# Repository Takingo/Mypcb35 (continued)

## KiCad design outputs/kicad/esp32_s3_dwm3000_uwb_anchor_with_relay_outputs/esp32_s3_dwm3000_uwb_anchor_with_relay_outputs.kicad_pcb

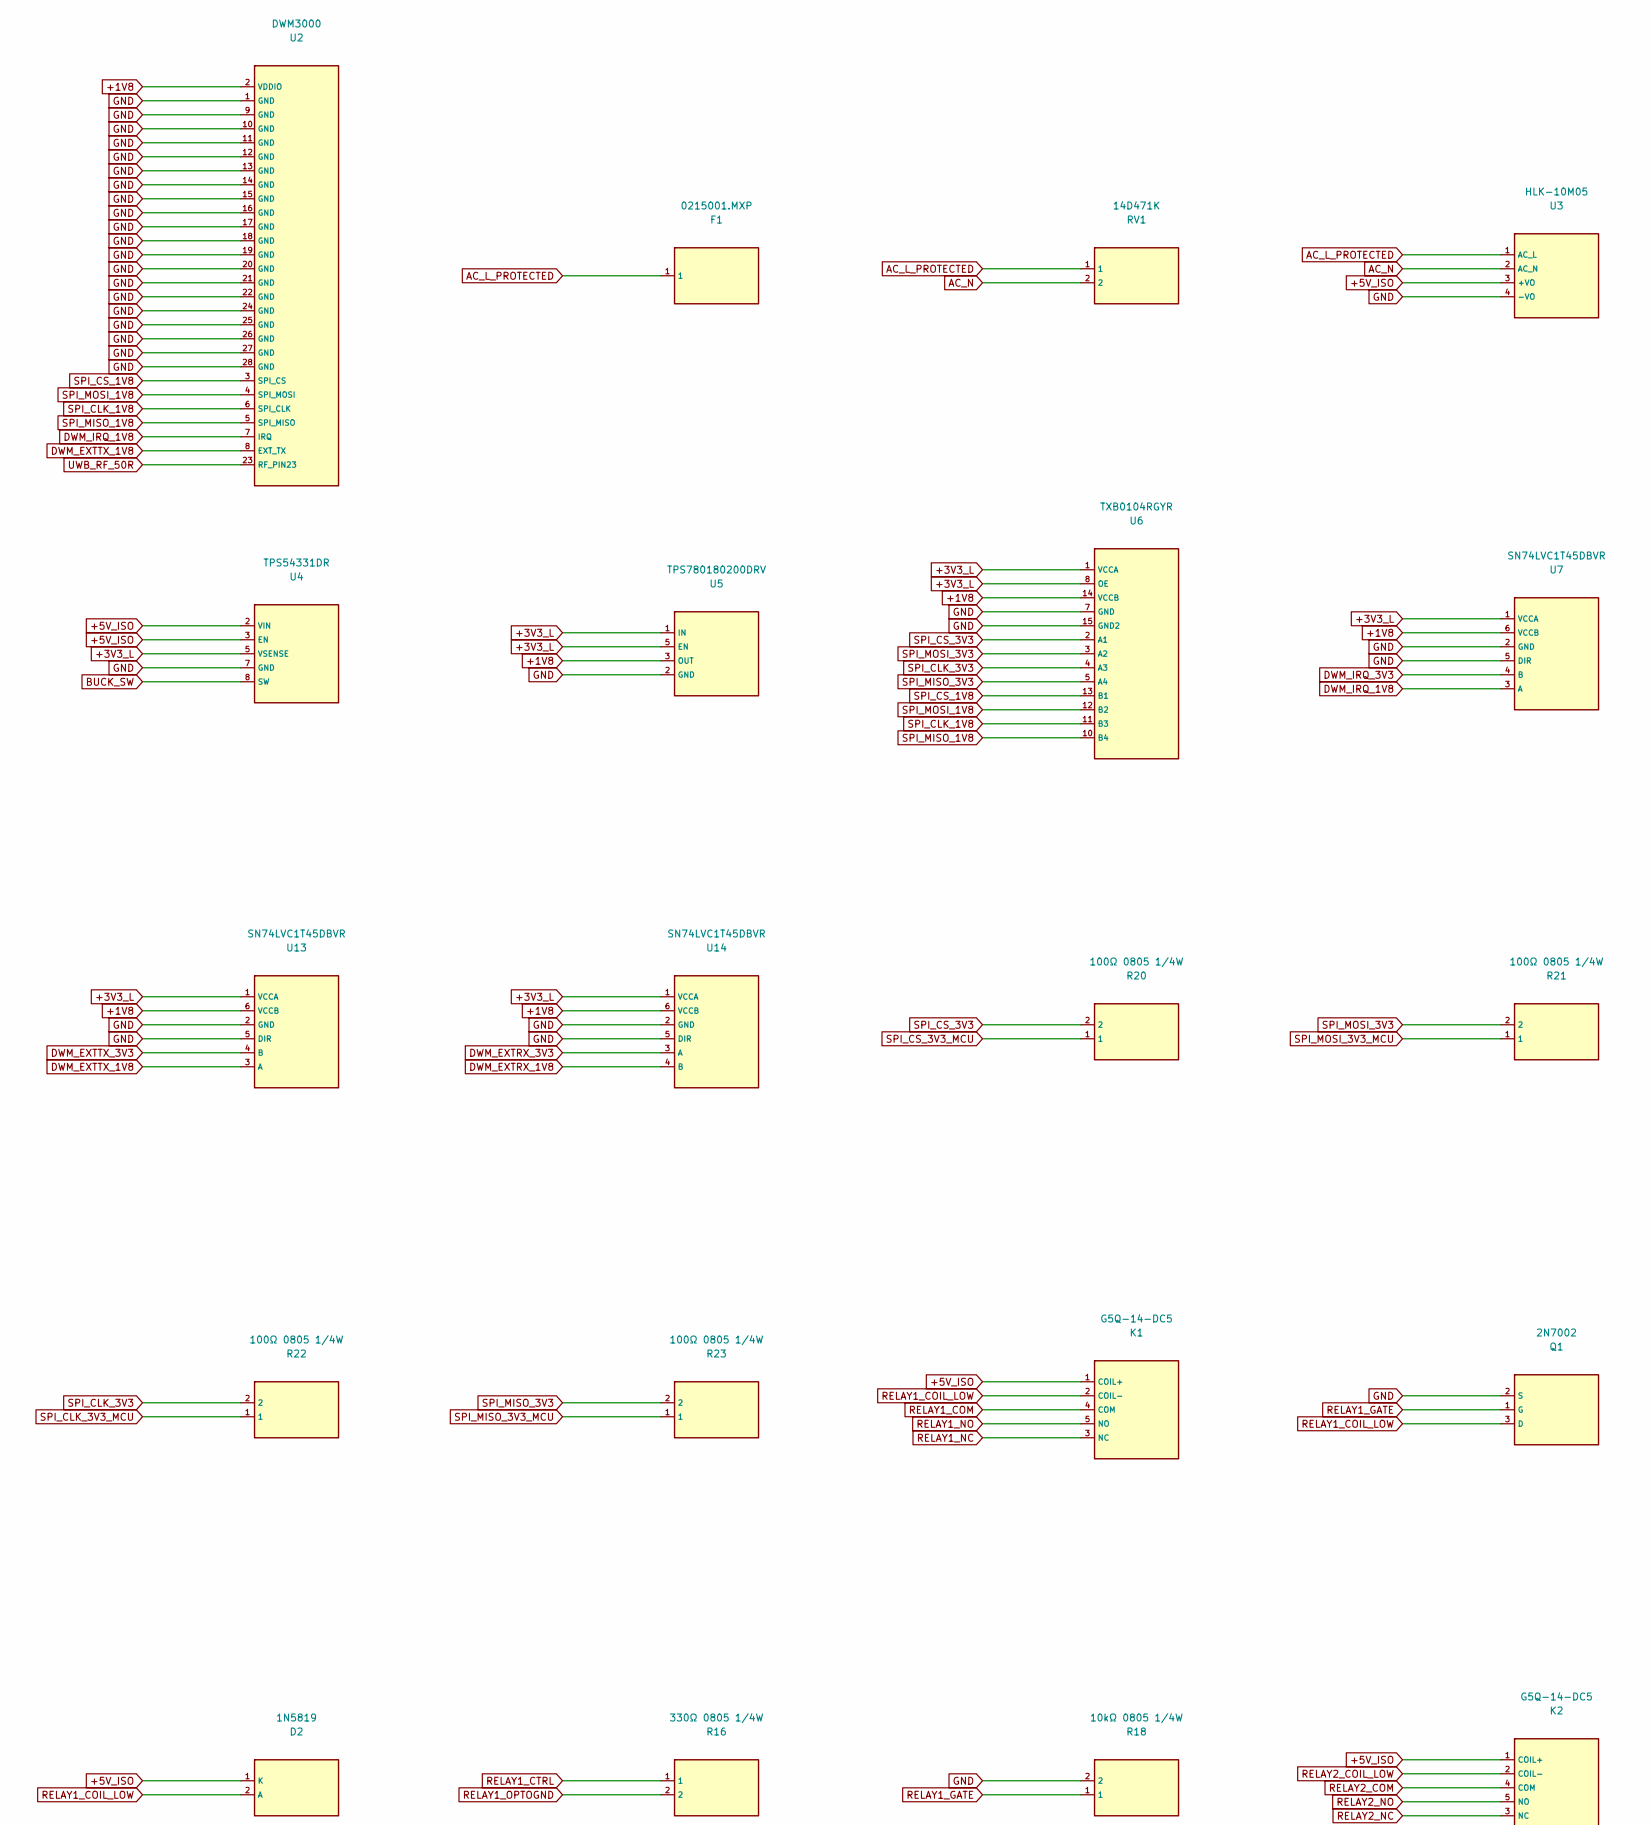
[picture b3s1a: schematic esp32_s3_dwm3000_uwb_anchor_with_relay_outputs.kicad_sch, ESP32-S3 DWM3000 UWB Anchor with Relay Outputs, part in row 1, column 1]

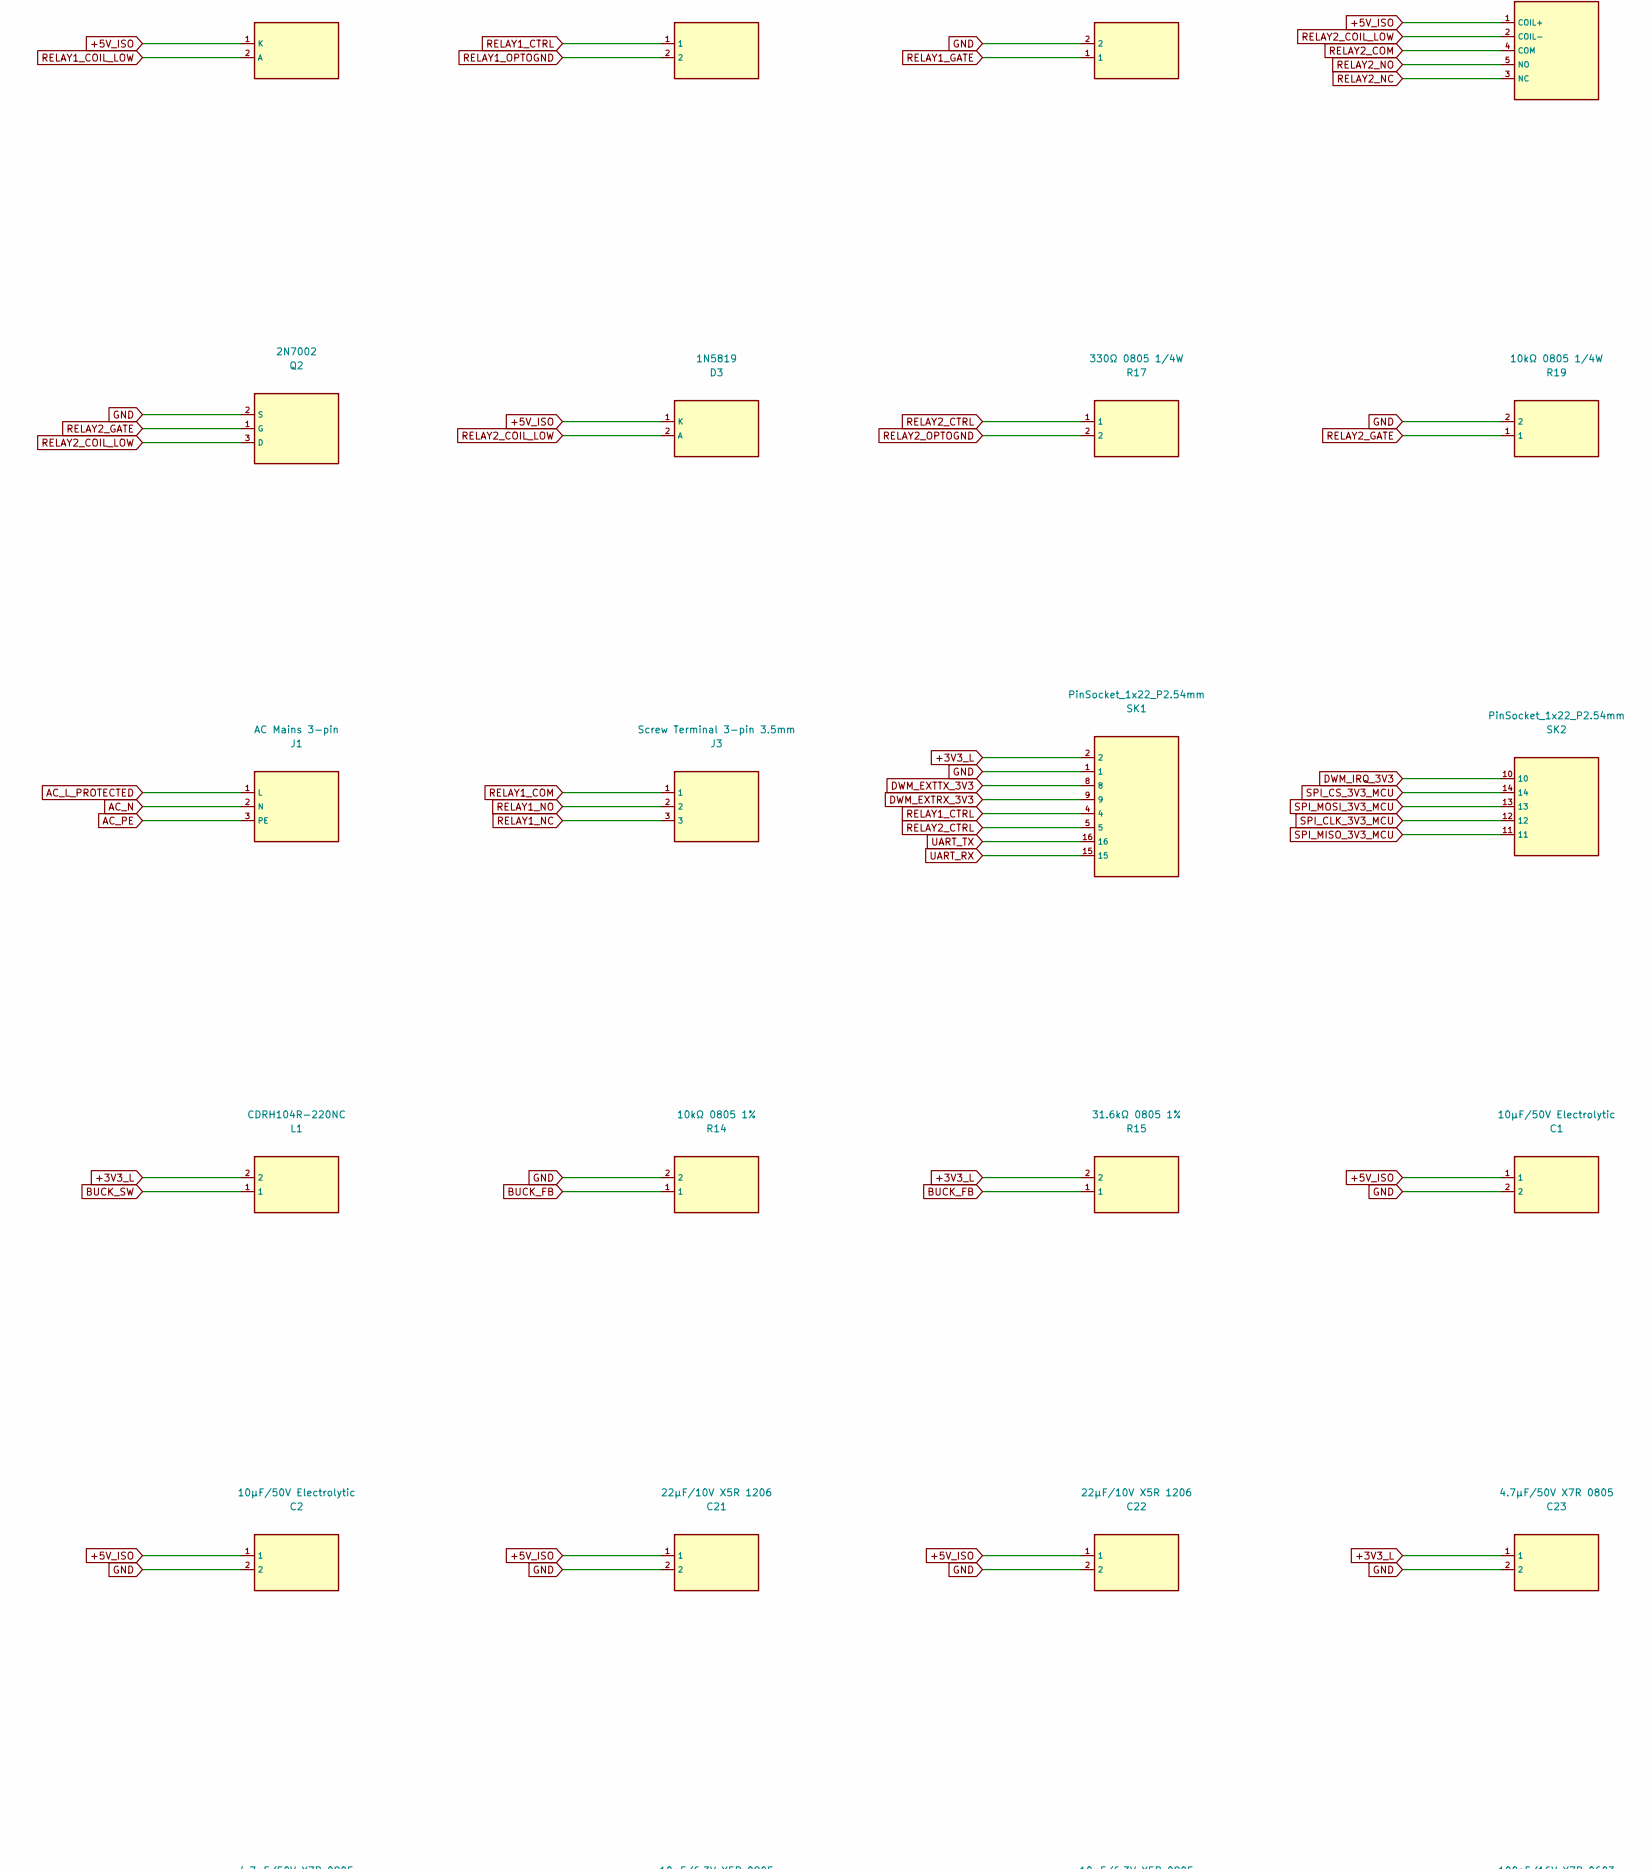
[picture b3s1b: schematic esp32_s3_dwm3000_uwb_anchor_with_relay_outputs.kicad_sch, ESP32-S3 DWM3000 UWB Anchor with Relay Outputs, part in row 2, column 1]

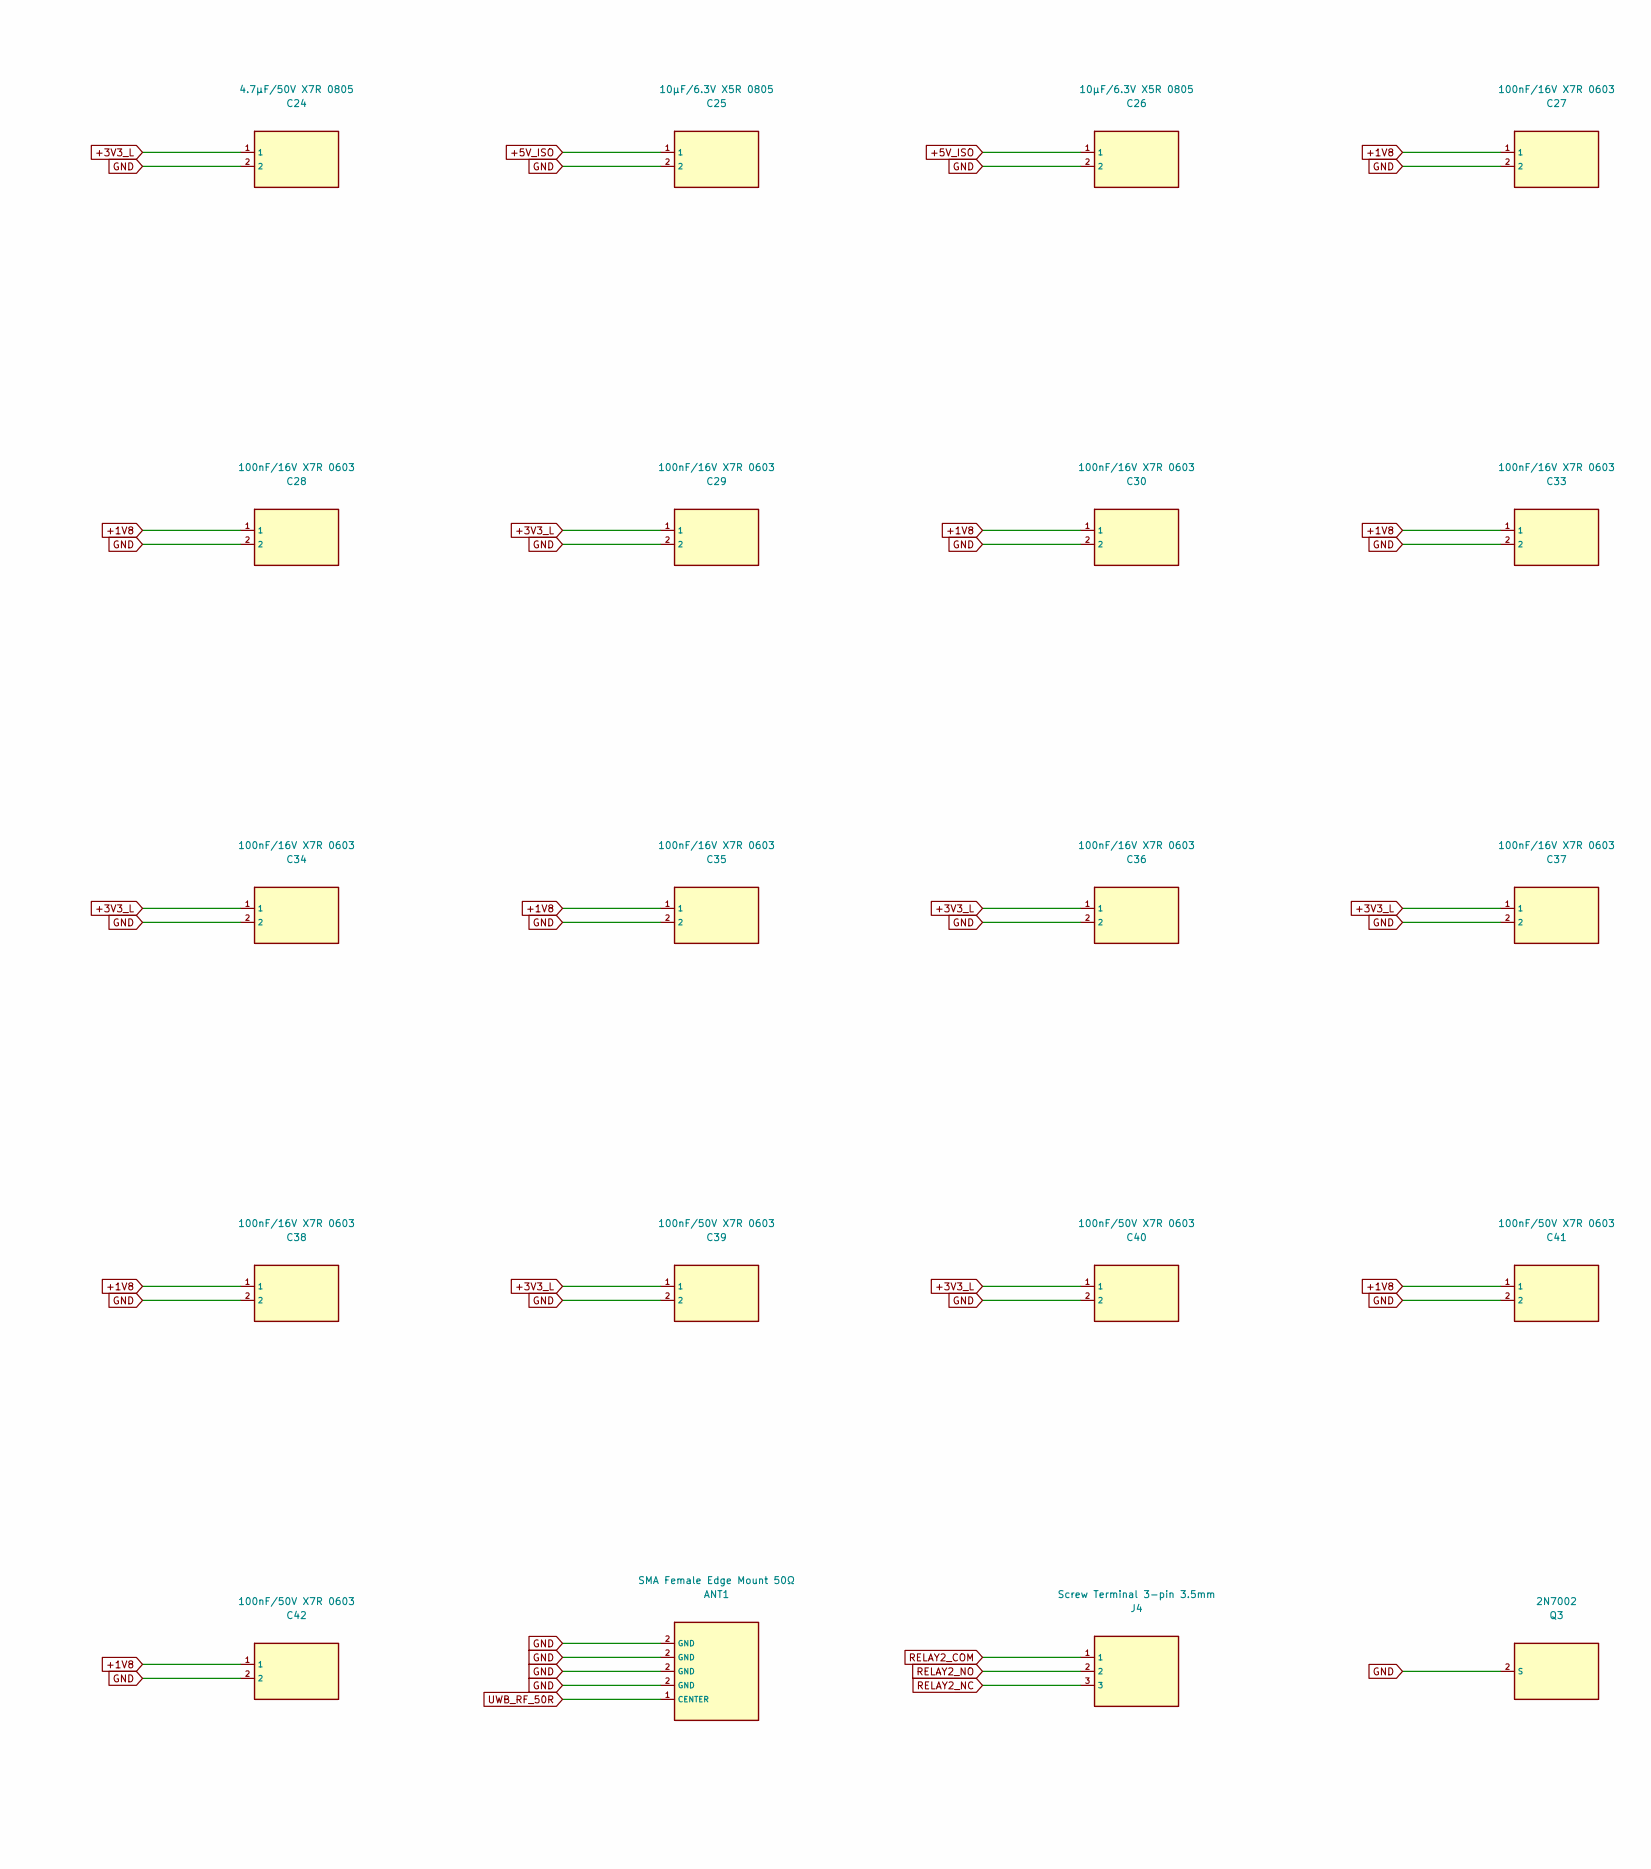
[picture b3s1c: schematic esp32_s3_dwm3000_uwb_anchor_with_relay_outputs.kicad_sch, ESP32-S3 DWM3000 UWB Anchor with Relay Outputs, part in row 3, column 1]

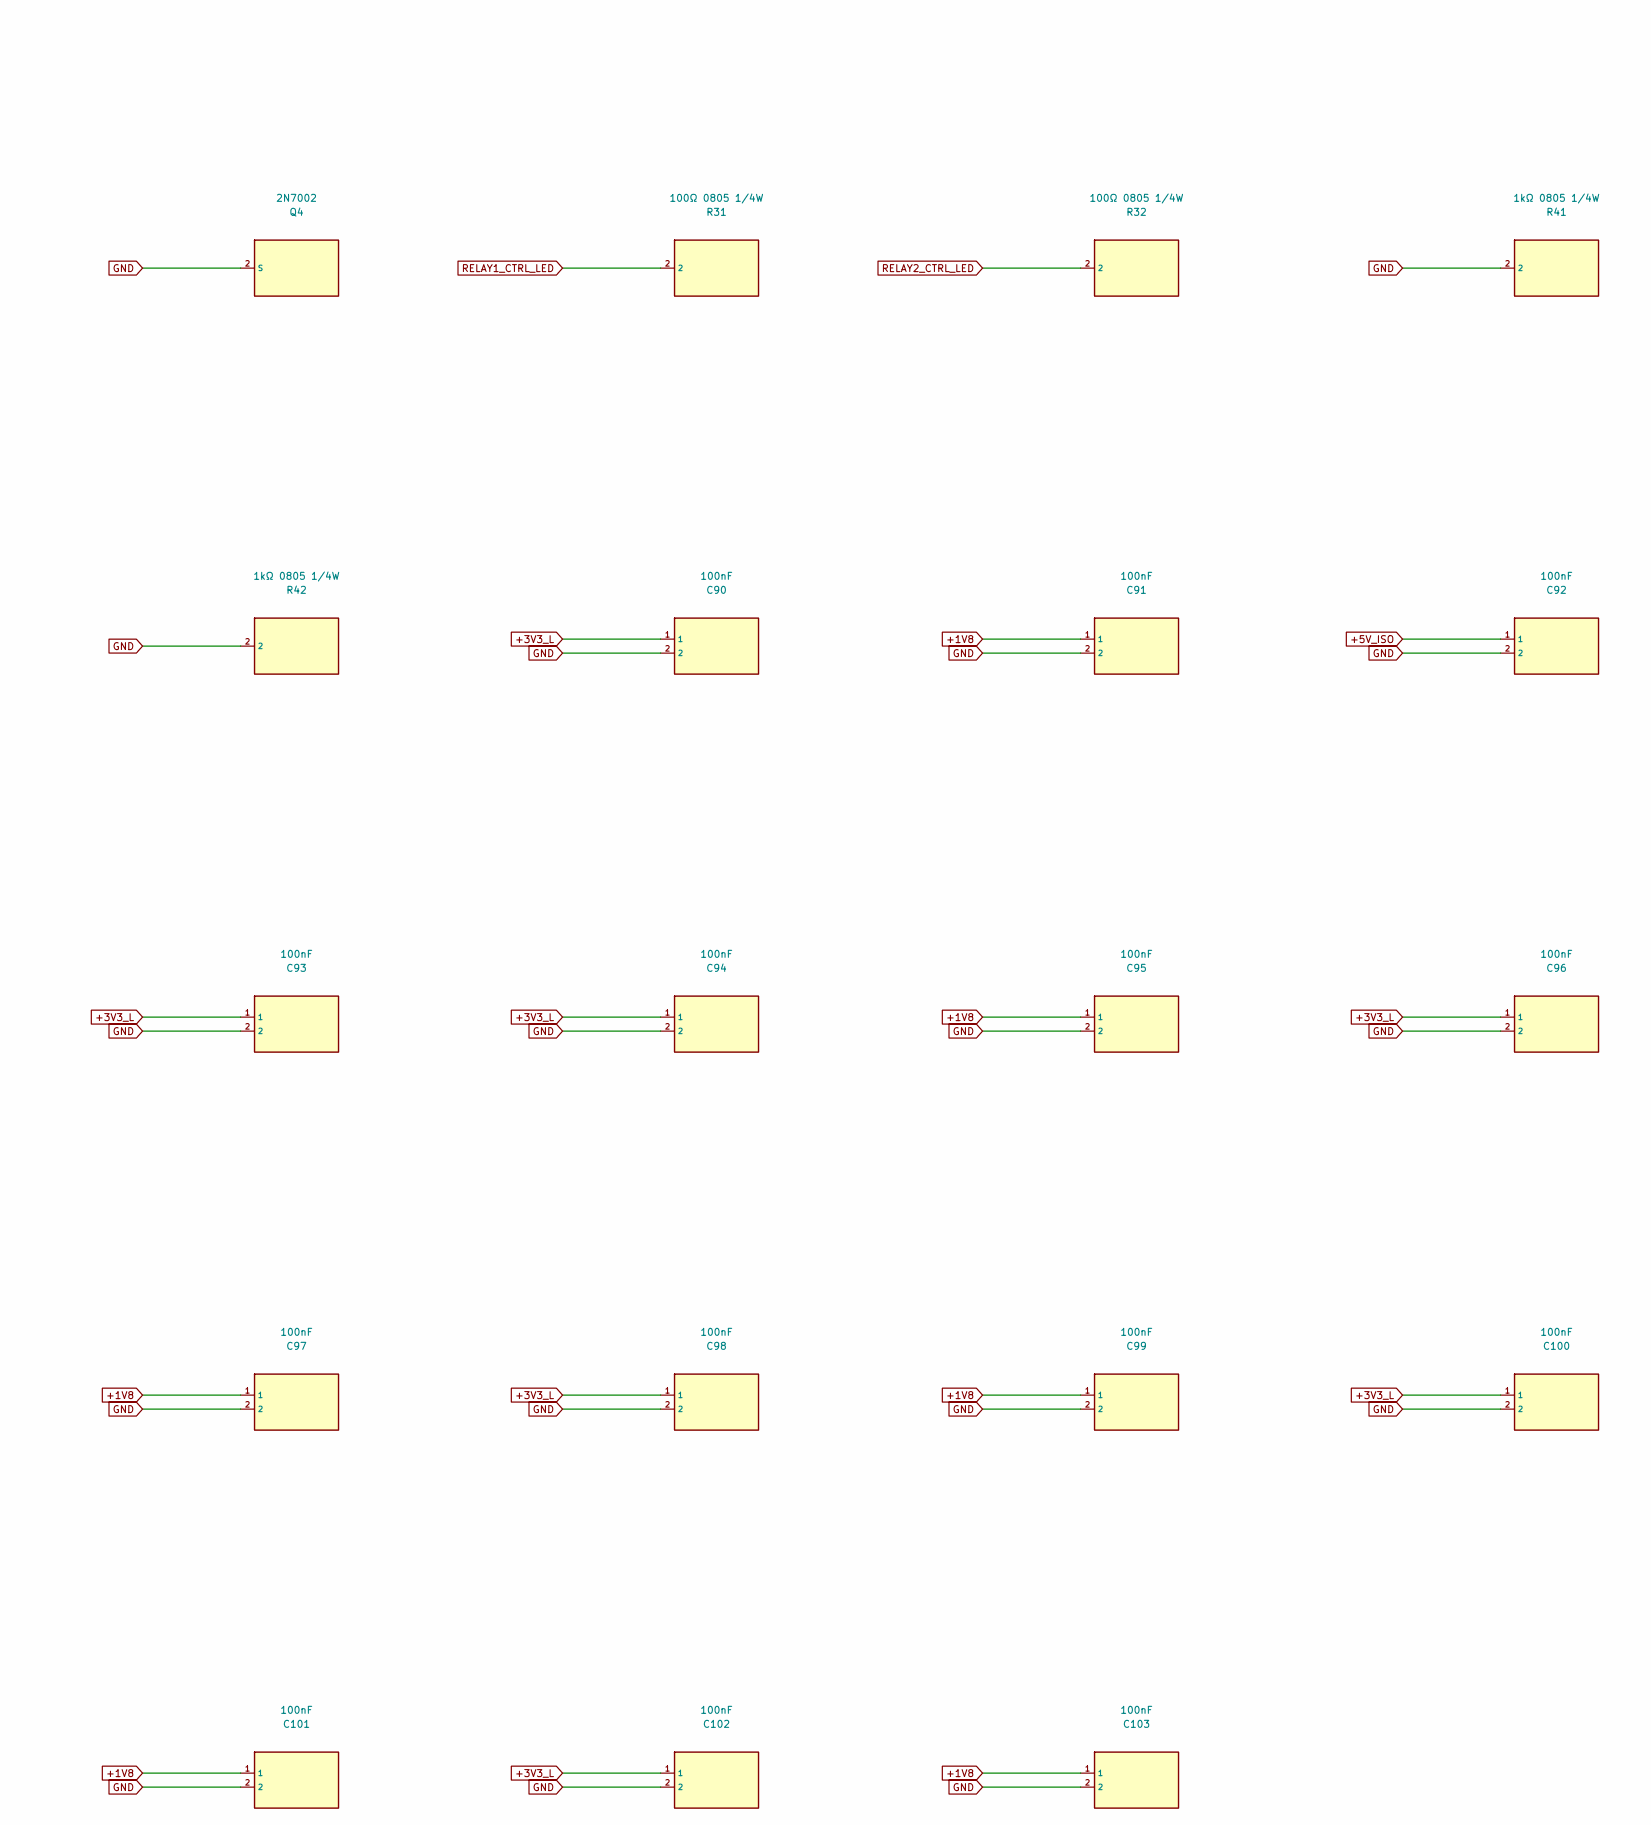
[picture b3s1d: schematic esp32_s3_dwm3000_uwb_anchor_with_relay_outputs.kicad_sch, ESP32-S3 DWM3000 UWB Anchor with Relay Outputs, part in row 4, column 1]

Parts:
ANT1: SMA Female Edge Mount 50Ω; SMA_Amphenol_132134_Vertical
C1, C2: 10µF/50V Electrolytic; CP_Radial_D5.0mm_P2.00mm
C21, C22: 22µF/10V X5R 1206; C_1206_3216Metric
C23, C24: 4.7µF/50V X7R 0805; C_0805_2012Metric
C25, C26: 10µF/6.3V X5R 0805; C_0805_2012Metric
C27, C28, C29, C30, C33, C34, C35, C36, C37, C38: 100nF/16V X7R 0603; C_0603_1608Metric
C39, C40, C41, C42: 100nF/50V X7R 0603; C_0603_1608Metric
C90, C91, C92, C93, C94, C95, C96, C97, C98, C99, C100, C101, C102, C103: 100nF; C_0603_1608Metric
D2, D3: 1N5819; D_SMA
F1: 0215001.MXP; Fuseholder_Littelfuse_100_series_5x20mm
J1: AC Mains 3-pin; TerminalBlock_Phoenix_PT-1,5-3-5.0-H_1x03_P5.00mm_Horizontal
J3, J4: Screw Terminal 3-pin 3.5mm; TerminalBlock_Phoenix_PT-1,5-3-3.5-H_1x03_P3.50mm_Horizontal
K1, K2: G5Q-14-DC5; Relay_SPDT_Omron-G5Q-1
L1: CDRH104R-220NC; L_10.4x10.4_H4.8
Q1, Q2, Q3, Q4: 2N7002; SOT-23
R14: 10kΩ 0805 1%; R_0805_2012Metric
R15: 31.6kΩ 0805 1%; R_0805_2012Metric
R16, R17: 330Ω 0805 1/4W; R_0805_2012Metric
R18, R19: 10kΩ 0805 1/4W; R_0805_2012Metric
R20, R21, R22, R23, R31, R32: 100Ω 0805 1/4W; R_0805_2012Metric
R41, R42: 1kΩ 0805 1/4W; R_0805_2012Metric
RV1: 14D471K; RV_Disc_D15.5mm_W4.5mm_P7.5mm
SK1, SK2: PinSocket_1x22_P2.54mm; PinSocket_1x22_P2.54mm_Vertical
U2: DWM3000
U3: HLK-10M05; Converter_ACDC_Hi-Link_HLK-10Mxx
U4: TPS54331DR; SOIC-8_3.9x4.9mm_P1.27mm
U5: TPS780180200DRV; SOT-23-5
U6: TXB0104RGYR; WQFN-14-1EP_2.5x2.5mm_P0.5mm_EP1.45x1.45mm
U7, U13, U14: SN74LVC1T45DBVR; SOT-23-6

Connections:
+1V8: C27.1, C28.1, C30.1, C33.1, C35.1, C38.1, C41.1, C42.1, C91.1, C95.1, C97.1, C99.1, C101.1, C103.1, U2.2 (VDDIO), U5.3 (OUT), U6.14 (VCCB), U7.6 (VCCB), U13.6 (VCCB), U14.6 (VCCB)
+3V3_L: C23.1, C24.1, C29.1, C34.1, C36.1, C37.1, C39.1, C40.1, C90.1, C93.1, C94.1, C96.1, C98.1, C100.1, C102.1, L1.2, R15.2, SK1.2, U4.5 (VSENSE), U5.1 (IN), U5.5 (EN), U6.1 (VCCA), U6.8 (OE), U7.1 (VCCA), U13.1 (VCCA), U14.1 (VCCA)
+5V_ISO: C1.1, C2.1, C21.1, C22.1, C25.1, C26.1, C92.1, D2.1 (K), D3.1 (K), K1.1 (COIL+), K2.1 (COIL+), U3.3 (+VO), U4.2 (VIN), U4.3 (EN)
AC_L_PROTECTED: F1.1, J1.1 (L), RV1.1, U3.1 (AC_L)
AC_N: J1.2 (N), RV1.2, U3.2 (AC_N)
AC_PE: J1.3 (PE)
BUCK_FB: R14.1, R15.1
BUCK_SW: L1.1, U4.8 (SW)
DWM_EXTRX_1V8: U14.4 (B)
DWM_EXTRX_3V3: SK1.9, U14.3 (A)
DWM_EXTTX_1V8: U2.8 (EXT_TX), U13.3 (A)
DWM_EXTTX_3V3: SK1.8, U13.4 (B)
DWM_IRQ_1V8: U2.7 (IRQ), U7.3 (A)
DWM_IRQ_3V3: SK2.10, U7.4 (B)
GND: ANT1.2 (GND), C1.2, C2.2, C21.2, C22.2, C23.2, C24.2, C25.2, C26.2, C27.2, C28.2, C29.2, C30.2, C33.2, C34.2, C35.2, C36.2, C37.2, C38.2, C39.2, C40.2, C41.2, C42.2, C90.2, C91.2, C92.2, C93.2, C94.2, C95.2, C96.2, C97.2, C98.2, C99.2, C100.2, C101.2, C102.2, C103.2, Q1.2 (S), Q2.2 (S), Q3.2, Q4.2, R14.2, R18.2, R19.2, R41.2, R42.2, SK1.1, U2.1 (GND), U2.9 (GND), U2.10 (GND), U2.11 (GND), U2.12 (GND), U2.13 (GND), U2.14 (GND), U2.15 (GND), U2.16 (GND), U2.17 (GND), U2.18 (GND), U2.19 (GND), U2.20 (GND), U2.21 (GND), U2.22 (GND), U2.24 (GND), U2.25 (GND), U2.26 (GND), U2.27 (GND), U2.28 (GND), U3.4 (-VO), U4.7 (GND), U5.2 (GND), U6.7 (GND), U6.15 (GND2), U7.2 (GND), U7.5 (DIR), U13.2 (GND), U13.5 (DIR), U14.2 (GND), U14.5 (DIR)
RELAY1_COIL_LOW: D2.2 (A), K1.2 (COIL-), Q1.3 (D)
RELAY1_COM: J3.1, K1.4 (COM)
RELAY1_CTRL: R16.1, SK1.4
RELAY1_CTRL_LED: R31.2
RELAY1_GATE: Q1.1 (G), R18.1
RELAY1_NC: J3.3, K1.3 (NC)
RELAY1_NO: J3.2, K1.5 (NO)
RELAY1_OPTOGND: R16.2
RELAY2_COIL_LOW: D3.2 (A), K2.2 (COIL-), Q2.3 (D)
RELAY2_COM: J4.1, K2.4 (COM)
RELAY2_CTRL: R17.1, SK1.5
RELAY2_CTRL_LED: R32.2
RELAY2_GATE: Q2.1 (G), R19.1
RELAY2_NC: J4.3, K2.3 (NC)
RELAY2_NO: J4.2, K2.5 (NO)
RELAY2_OPTOGND: R17.2
SPI_CLK_1V8: U2.6 (SPI_CLK), U6.11 (B3)
SPI_CLK_3V3: R22.2, U6.4 (A3)
SPI_CLK_3V3_MCU: R22.1, SK2.12
SPI_CS_1V8: U2.3 (SPI_CS), U6.13 (B1)
SPI_CS_3V3: R20.2, U6.2 (A1)
SPI_CS_3V3_MCU: R20.1, SK2.14
SPI_MISO_1V8: U2.5 (SPI_MISO), U6.10 (B4)
SPI_MISO_3V3: R23.2, U6.5 (A4)
SPI_MISO_3V3_MCU: R23.1, SK2.11
SPI_MOSI_1V8: U2.4 (SPI_MOSI), U6.12 (B2)
SPI_MOSI_3V3: R21.2, U6.3 (A2)
SPI_MOSI_3V3_MCU: R21.1, SK2.13
UART_RX: SK1.15
UART_TX: SK1.16
UWB_RF_50R: ANT1.1 (CENTER), U2.23 (RF_PIN23)

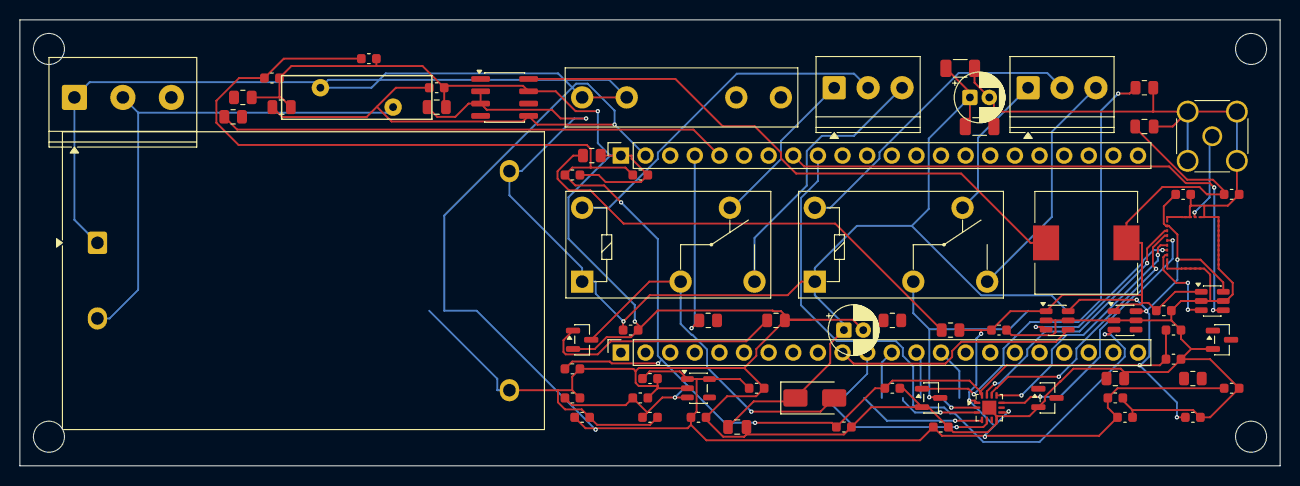
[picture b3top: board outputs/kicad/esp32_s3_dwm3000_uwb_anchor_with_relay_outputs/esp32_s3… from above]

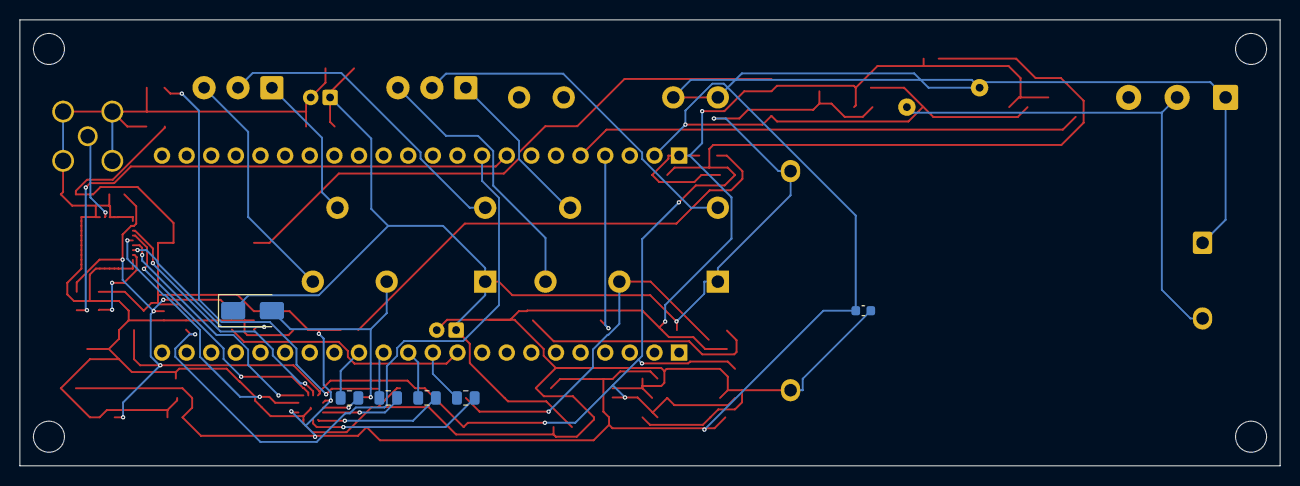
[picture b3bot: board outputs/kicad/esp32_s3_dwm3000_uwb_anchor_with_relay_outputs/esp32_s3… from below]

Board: 4 copper layers, 130.0 x 46.0 mm, 75 parts (6 on the bottom side), 38 nets.

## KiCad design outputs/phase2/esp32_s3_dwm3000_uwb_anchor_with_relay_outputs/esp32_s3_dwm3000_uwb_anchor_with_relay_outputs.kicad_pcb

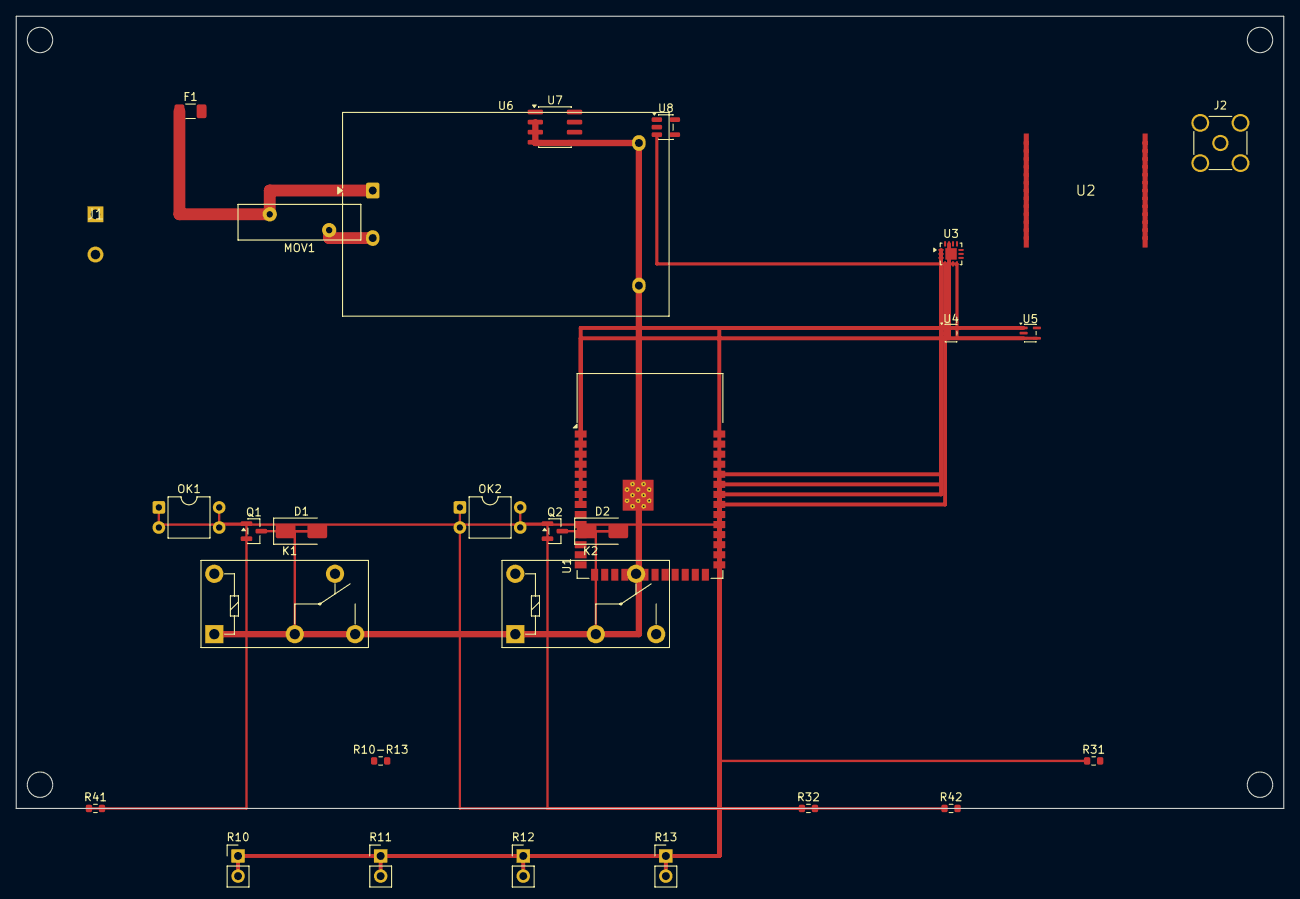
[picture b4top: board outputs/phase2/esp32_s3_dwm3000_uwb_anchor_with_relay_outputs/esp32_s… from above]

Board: 2 copper layers, 160.0 x 100.0 mm, 29 parts (0 on the bottom side), 18 nets.

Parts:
D1, D2: SS14; D_SMA
F1: 500mA; Fuse_1206_3216Metric
J1: AC Şebeke Girişi
J2: SMA Anten Konektörü; SMA_Amphenol_901-144_Vertical
K1, K2: 5V relay; Relay_SPDT_Omron-G5Q-1
MOV1: MOV 471VAC; RV_Disc_D15.5mm_W4.5mm_P7.5mm
OK1, OK2: PC817; DIP-4_W7.62mm
Q1, Q2: 2N7002; SOT-23
R10, R11, R12, R13: Harici Konektör; PinHeader_1x02_P2.54mm_Vertical
R10-R13: 100R; R_0603_1608Metric
R31, R32: 330R; R_0603_1608Metric
R41, R42: 100K; R_0603_1608Metric
U1: ESP32-S3 module; ESP32-S3-WROOM-1
U2: DWM3000
U3: 4-bit bidirectional; WQFN-14-1EP_2.5x2.5mm_P0.5mm_EP1.45x1.45mm
U4, U5: single-bit dual-supply; SOT-353_SC-70-5
U6: 5V isolated; Converter_ACDC_Hi-Link_HLK-5Mxx
U7: 3.3V; SOIC-8_3.9x4.9mm_P1.27mm
U8: 1.8V low-noise; SOT-23-5

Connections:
+1V8: U3.7, U4.4, U5.4, U8.3
+3V3: U1.2, U3.13, U4.3, U5.3
+5V_ISO: K1.1, K2.1, U6.3, U7.2
AC_L_PROTECTED: F1.1, MOV1.1, U6.1
AC_N: MOV1.2, U6.2
DWM_EXT_TX_3V3: U1.8, U5.1
DWM_IRQ_3V3: U1.32, U4.1
GND: U1.1, U6.4, U8.2
RELAY1_COIL_LOW: D1.2, K1.2, Q1.3
RELAY1_CTRL: OK1.1, R31.1, U1.31
RELAY1_GATE: OK1.4, Q1.1, R41.1
RELAY2_COIL_LOW: D2.2, K2.2, Q2.3
RELAY2_CTRL: OK2.1, R32.1
RELAY2_GATE: OK2.4, Q2.1, R42.1
SPI_CLK_3V3: R12.1, R12.2, U1.34, U3.3
SPI_CS_3V3: R10.1, R10.2, U1.36, U3.1
SPI_MISO_3V3: R13.1, R13.2, U1.33, U3.4
SPI_MOSI_3V3: R11.1, R11.2, U1.35, U3.2

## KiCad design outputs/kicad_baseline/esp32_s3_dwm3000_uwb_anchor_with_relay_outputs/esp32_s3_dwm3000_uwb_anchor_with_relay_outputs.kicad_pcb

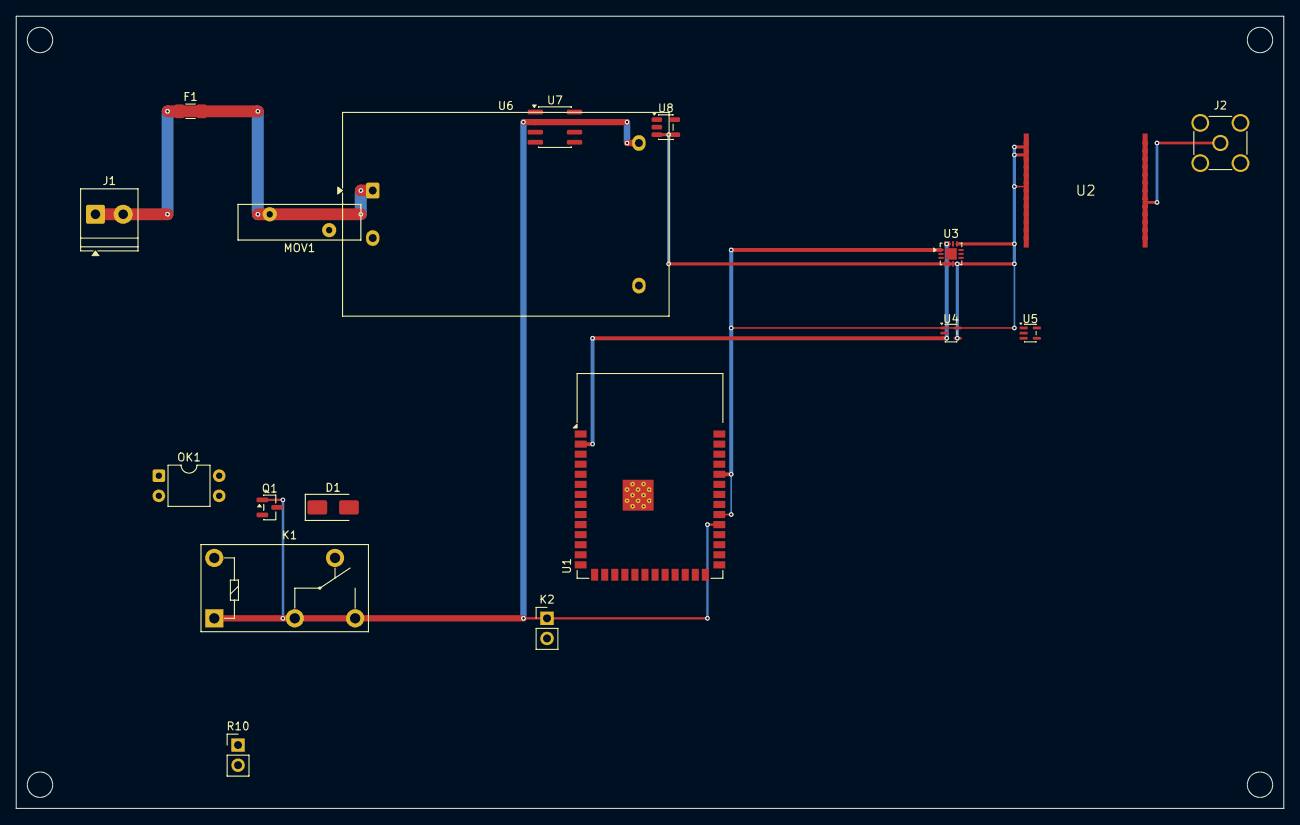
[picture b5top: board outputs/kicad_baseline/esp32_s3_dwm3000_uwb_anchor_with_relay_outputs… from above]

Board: 2 copper layers, 160.0 x 100.0 mm, 18 parts (0 on the bottom side), 9 nets.

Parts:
D1: SS14; D_SMA
F1: 500mA; Fuse_1206_3216Metric
J1: AC Şebeke Girişi; TerminalBlock_Phoenix_PT-1,5-2-3.5-H_1x02_P3.50mm_Horizontal
J2: SMA Anten Konektörü; SMA_Amphenol_901-144_Vertical
K1: 5V relay; Relay_SPDT_Omron-G5Q-1
K2: Harici Konektör; PinHeader_1x02_P2.54mm_Vertical
MOV1: 471VAC MOV; RV_Disc_D15.5mm_W4.5mm_P7.5mm
OK1: PC817; DIP-4_W7.62mm
Q1: 2N7002; SOT-23
R10: Harici Konektör; PinHeader_1x02_P2.54mm_Vertical
U1: ESP32-S3; ESP32-S3-WROOM-1
U2: DWM3000
U3: 4-bit bidirectional; WQFN-14-1EP_2.5x2.5mm_P0.5mm_EP1.45x1.45mm
U4, U5: single-bit dual-supply; SOT-353_SC-70-5
U6: 5V isolated; Converter_ACDC_Hi-Link_HLK-5Mxx
U7: 3.3V; SOIC-8_3.9x4.9mm_P1.27mm
U8: 1.8V low-noise; SOT-23-5

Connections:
+1V8: U2.2, U3.7, U4.4, U8.3
+3V3: U1.2, U3.13, U4.3
+5V_ISO: K1.1, U6.3, U7.2
AC_L_PROTECTED: F1.1, J1.1, MOV1.1, U6.1
DWM_IRQ: U1.32, U2.7, U4.1, U4.5
RELAY1_DRIVE: K1.2, Q1.1, U1.31
SPI_CS_1V8: U2.3, U3.11
SPI_CS_3V3: U1.36, U3.1
UWB_RF_50R: J2.1, U2.23

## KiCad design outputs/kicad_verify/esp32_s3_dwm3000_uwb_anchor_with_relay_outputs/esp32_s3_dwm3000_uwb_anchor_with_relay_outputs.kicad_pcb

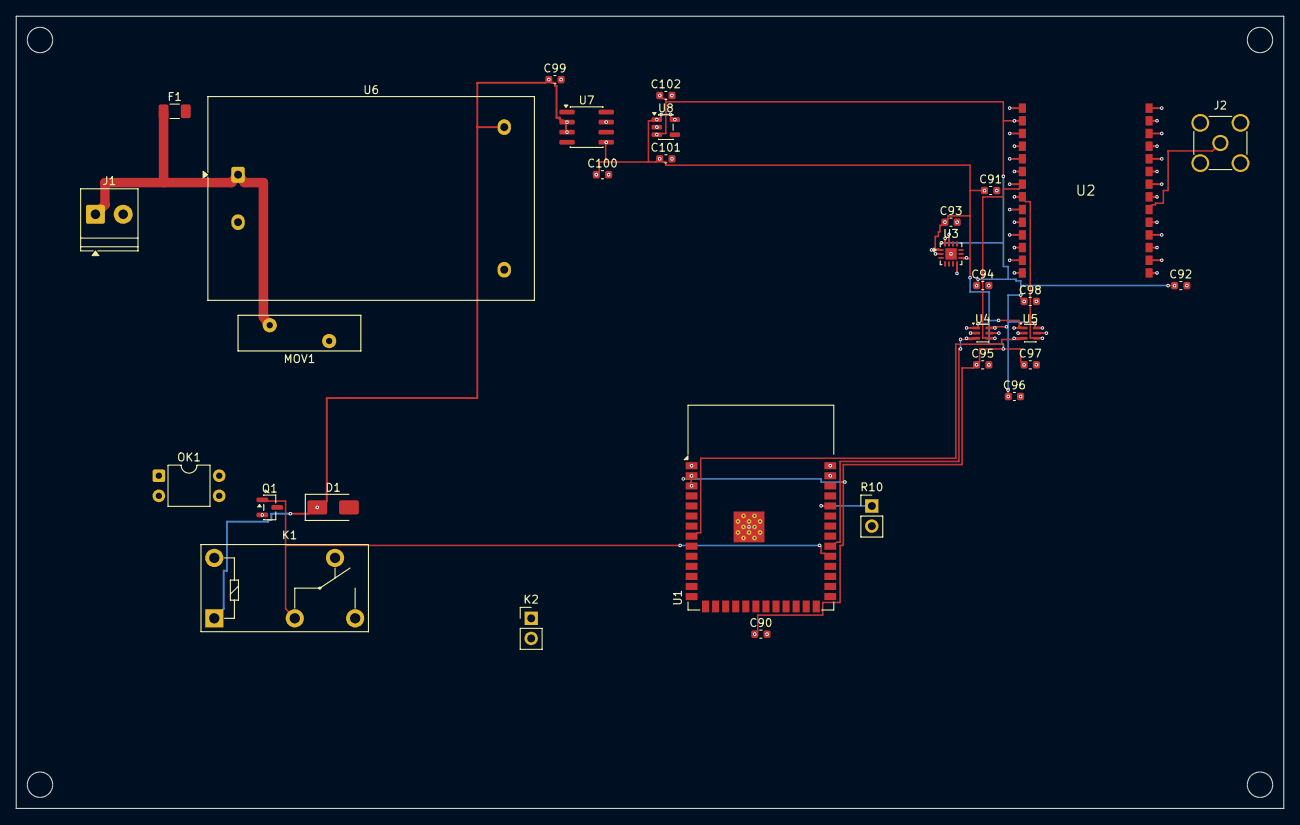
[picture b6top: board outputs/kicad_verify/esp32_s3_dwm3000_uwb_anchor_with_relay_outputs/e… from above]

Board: 4 copper layers, 160.0 x 100.0 mm, 31 parts (0 on the bottom side), 13 nets.

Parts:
C90, C91, C92, C93, C94, C95, C96, C97, C98, C99, C100, C101, C102: 100nF; C_0603_1608Metric
D1: SS14; D_SMA
F1: 500mA; Fuse_1206_3216Metric
J1: AC Şebeke Girişi; TerminalBlock_Phoenix_PT-1,5-2-3.5-H_1x02_P3.50mm_Horizontal
J2: SMA Anten Konektörü; SMA_Amphenol_901-144_Vertical
K1: 5V relay; Relay_SPDT_Omron-G5Q-1
K2: Harici Konektör; PinHeader_1x02_P2.54mm_Vertical
MOV1: 471VAC MOV; RV_Disc_D15.5mm_W4.5mm_P7.5mm
OK1: PC817; DIP-4_W7.62mm
Q1: 2N7002; SOT-23
R10: Harici Konektör; PinHeader_1x02_P2.54mm_Vertical
U1: ESP32-S3; ESP32-S3-WROOM-1
U2: DWM3000
U3: 4-bit bidirectional; WQFN-14-1EP_2.5x2.5mm_P0.5mm_EP1.45x1.45mm
U4, U5: single-bit dual-supply; SOT-363_SC-70-6
U6: 5V isolated; Converter_ACDC_Hi-Link_HLK-5Mxx
U7: 3.3V; SOIC-8_3.9x4.9mm_P1.27mm
U8: 1.8V low-noise; SOT-23-5

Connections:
+1V8: C92.1, C94.1, C96.1, C98.1, C102.1, U2.2, U3.14, U4.6, U5.6, U8.3
+3V3: C90.1, C91.1, C93.1, C95.1, C97.1, C100.1, C101.1, U1.2, U1.3, U3.1, U3.8, U4.1, U5.1, U7.5, U8.1, U8.5
+5V_ISO: C99.1, D1.1, K1.1, U6.3, U7.2, U7.3
AC_L_PROTECTED: F1.1, J1.1, MOV1.1, U6.1
DWM_EXT_TX_1V8: U2.8, U5.4
DWM_EXT_TX_3V3: U1.8, U5.3
DWM_IRQ_1V8: U2.7, U4.4
DWM_IRQ_3V3: U1.32, U4.3
GND: C90.2, C91.2, C92.2, C93.2, C94.2, C95.2, C96.2, C97.2, C98.2, C99.2, C100.2, C101.2, C102.2, J2.2, OK1.2, Q1.2, U1.1, U1.39, U1.40, U1.41, U2.1, U2.4, U2.5, U2.6, U2.9, U2.10, U2.11, U2.12, U2.13, U2.14, U2.15, U2.16, U2.17, U2.18, U2.19, U2.20, U2.21, U2.22, U2.24, U2.25, U2.26, U2.27, U2.28, U3.7, U3.15, U4.2, U4.5, U5.2, U5.5, U6.4, U7.7, U8.2
RELAY1_DRIVE: K1.2, Q1.1, U1.31
SPI_CS_1V8: U2.3, U3.13
SPI_CS_3V3_MCU: R10.1, U1.36
UWB_RF_50R: J2.1, U2.23

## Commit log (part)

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2026-05-27 Fix PCBA manufacturing export: Unicode error + asset file sync
    - Fixed UnicodeEncodeError in pcba_manufacturing_export_service.py (checkmark → [OK])
    - Generated real manufacturing package: 27 Gerber files + BOM + documentation
    - Synchronized pcba_manufacturing_package.json to assets/generated/ for Flutter access
    - Verified both K1 and K2 relays present in schematic, PCB, and manufacturing BOM
    - Updated Brainmypcb documentation with manufacturing export status
    - Board size confirmed: 160×100 mm, 4-layer, 59 components, DRC clean
2026-05-27 CRITICAL FIX: Remove ghost capacitors (C99-C102) from PCB and schematic
    C99-C102 were in the PCB but NOT in the user's original BOM.csv
    This violated the design principle: system must match user's specifications exactly.
    Changes:
    - Removed C99-C102 symbol definitions from schematic (.kicad_sch)
    - Removed C99-C102 footprint instances from schematic
    - Removed C99-C102 footprint instances from PCB (.kicad_pcb)
2026-06-05 Implement full autonomous routing and AI synthesis loop
2026-06-06 fix: J2 footprint SMA->DC Jack (BarrelJack_CUI_PJ-002A_Horizontal)
    - J2 was incorrectly identified as SMA antenna connector
    - Fixed in _with_virtual_endpoint_components: comp_type = dc_power_jack
    - Fixed in _footprint_id_for_component: explicit J2 -> BarrelJack rule
    - Fixed in _footprint_for_component: loads BarrelJack_CUI_PJ-002A_Horizontal
    - Fixed pin resolver: J2 uses DC jack pin map (tip=1/VCC, sleeve=2/GND)
    - Fixed GND pad assignment: removed J2 from ANT1 SMA pad group
